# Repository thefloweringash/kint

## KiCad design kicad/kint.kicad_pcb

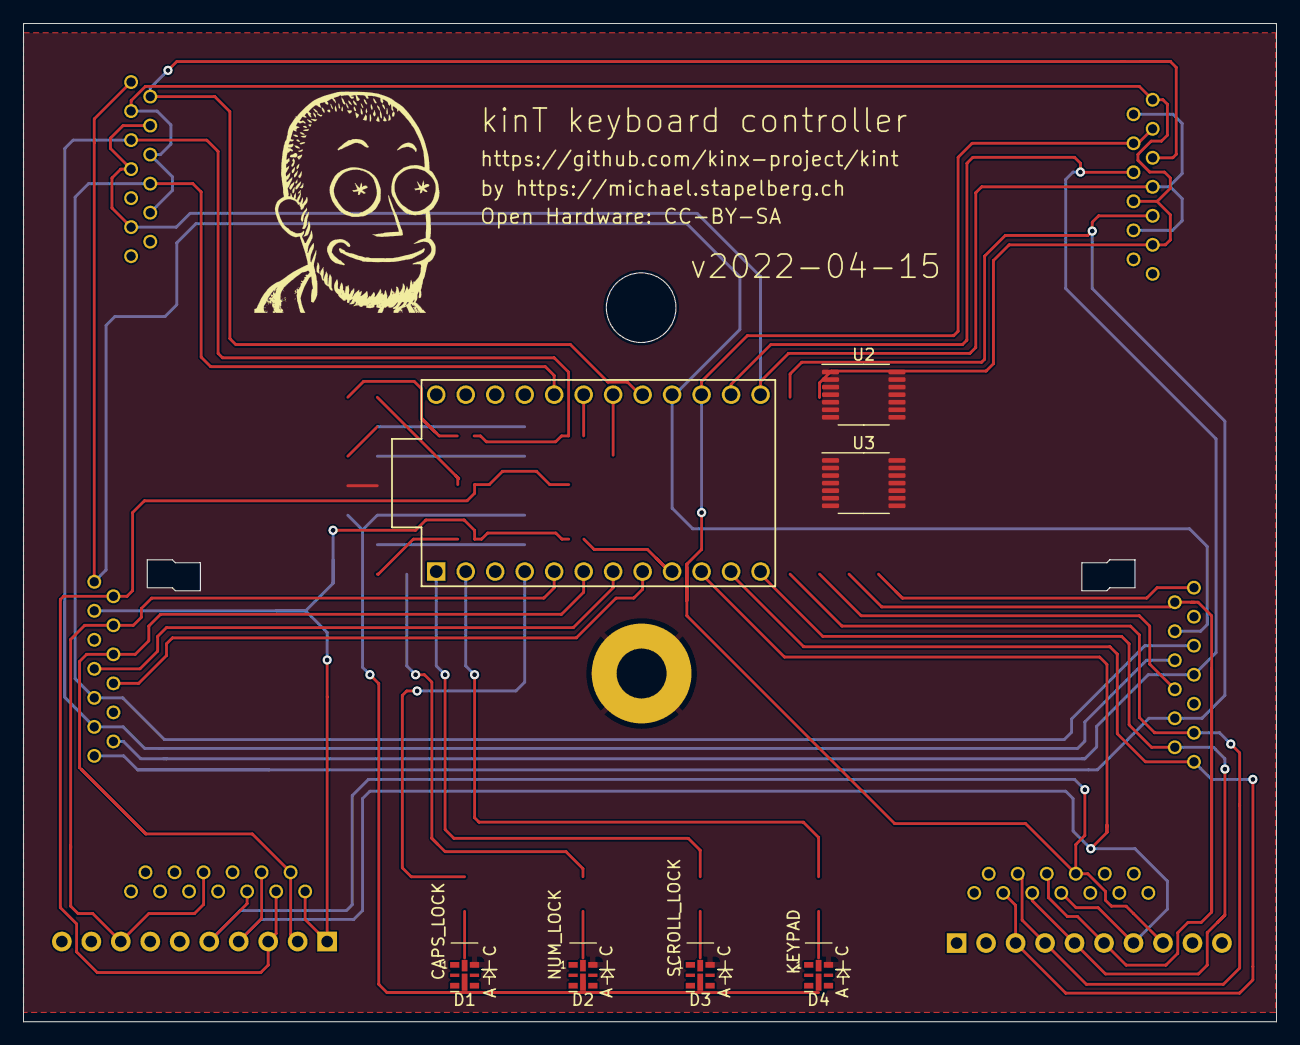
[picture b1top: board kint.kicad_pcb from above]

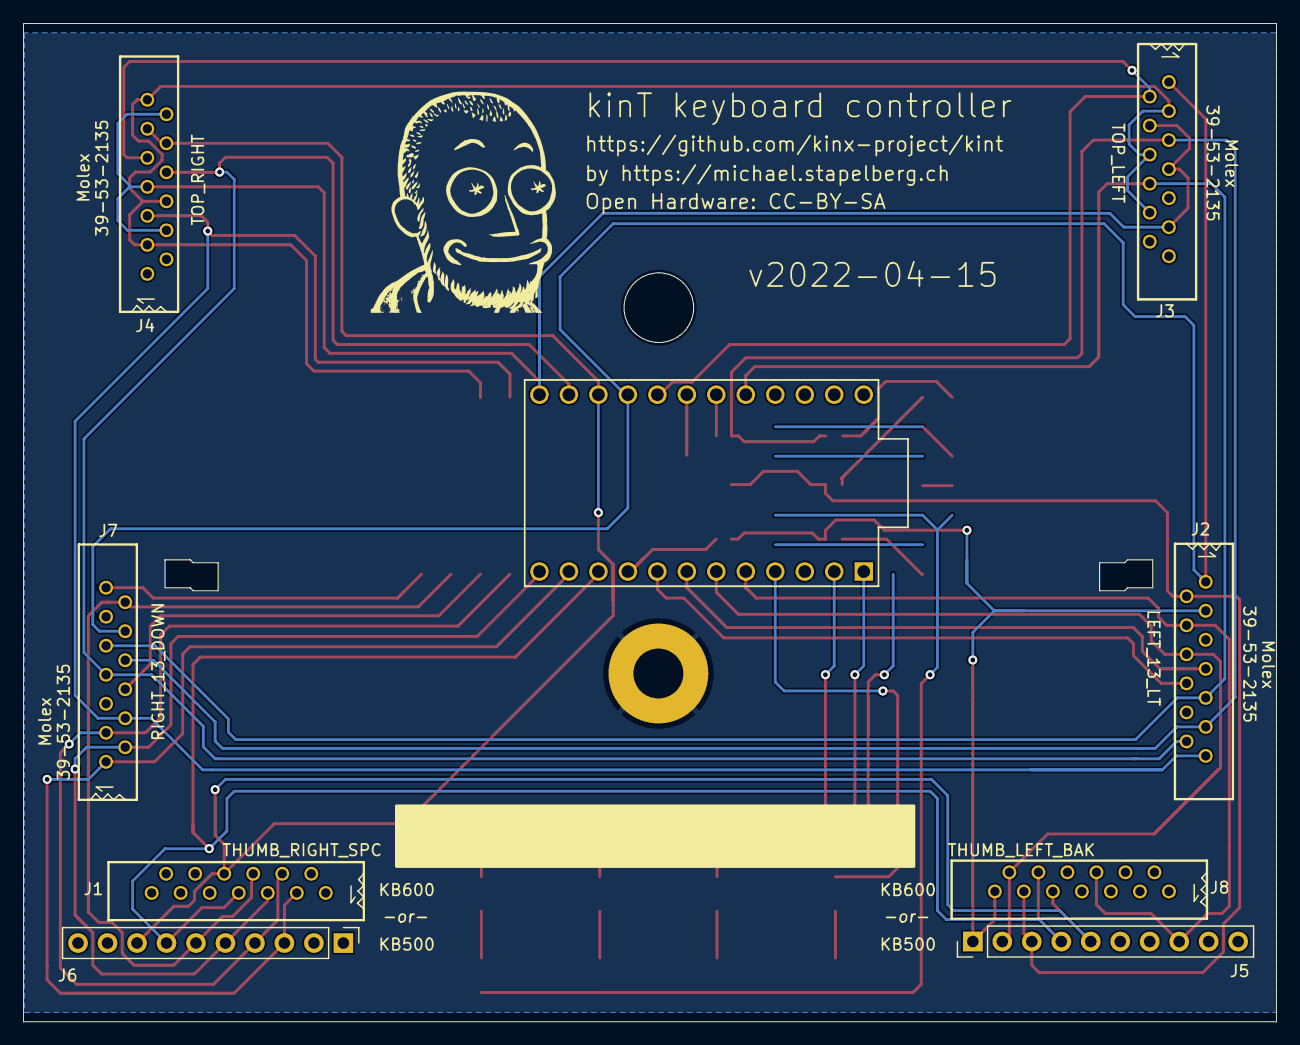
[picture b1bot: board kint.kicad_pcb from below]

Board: 2 copper layers, 107.9 x 86.0 mm, 17 parts (8 on the bottom side), 35 nets.

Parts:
D1, D2, D3, D4: APA102-2020; LED-APA102-2020
H1: mounting pad; MountingHole_4.3mm_M4_Pad
H2: mounting pad; MountingHole_6mm
J1: THUMB_RIGHT_SPC_KB600; 39-53-2135
J2: LEFT_13_LT; 39-53-2135
J3: TOP_LEFT; 39-53-2135
J4: TOP_RIGHT; 39-53-2135
J5: THUMB_LEFT_BAK; PinHeader_1x10_P2.54mm_Vertical
J6: THUMB_RIGHT_SPC; PinHeader_1x10_P2.54mm_Vertical
J7: RIGHT_13_DOWN; 39-53-2135
J8: THUMB_LEFT_BAK_KB600; 39-53-2135
U1: ProMicro
U2, U3: 74HC164; TSSOP-14_4.4x5mm_P0.65mm

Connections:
/5V: D1.1 (VDD), D2.1 (VDD), D3.1 (VDD), D4.1 (VDD)
/COL_0: J2.1, J3.1, J7.10, U1.20 (F4)
/COL_1: J2.9, J3.8, J7.9, U1.19 (F5)
/COL_2: J2.11, J3.5, J7.8, U1.18 (F6)
/COL_3: J2.12, J4.8, J7.7, U1.17 (F7)
/COL_4: J2.13, J4.5, J7.4, U1.16 (B1)
/COL_5: J1.8, J4.10, J4.11, J5.5, J6.8, J8.9, U1.15 (B3)
/COL_6: J1.7, J5.4, J6.7, J8.10, U1.14 (B2)
/LED_CLOCK: D1.5 (CKI), U1.6 (SCL)
/LED_DATA: D1.4 (SDI), U1.5 (SDA)
/ROW_0: J7.13, U2.3 (Q0)
/ROW_1: J2.7, U2.4 (Q1)
/ROW_2: J2.6, J5.2, J8.12, U2.5 (Q2)
/ROW_3: J2.4, J5.8, J8.6, U2.6 (Q3)
/ROW_4: J2.3, J5.1, J8.13, U2.10 (Q4)
/ROW_5: J2.2, J5.3, J8.11, U2.11 (Q5)
/ROW_6: J1.3, J6.3, J7.1, U2.12 (Q6)
/ROW_7: J1.4, J6.4, J7.3, U2.13 (Q7), U3.1 (DSA)
/ROW_8: J1.5, J6.5, J7.2, U3.3 (Q0)
/ROW_9: J1.6, J6.6, J7.12, U3.4 (Q1)
/ROW_CLOCK: U1.10 (E6), U2.8 (CP), U3.8 (CP)
/ROW_DATA: U1.9 (D7), U2.1 (DSA)
/ROW_EQL: J2.8, U3.12 (Q6)
/ROW_ESC: J3.2, J4.9, U3.11 (Q5)
/ROW_F1: J3.3, J3.6, J3.10, J4.3, J4.6, J4.13, U3.5 (Q2)
/ROW_F2: J3.4, J3.7, J3.11, J4.4, J4.7, J4.12, U3.6 (Q3)
/ROW_MIN: J7.6, U3.10 (Q4)
/VCC: U2.14 (VCC), U3.14 (VCC)
GND: D1.6 (GND), D2.6 (GND), D3.6 (GND), D4.6 (GND), H1.1, U1.3 (GND), U1.4 (GND), U1.23 (GND), U2.7 (GND), U3.7 (GND)
unnamed: D1.2 (CKO), D2.5 (CKI)
unnamed: D1.3 (SDO), D2.4 (SDI)
unnamed: D2.2 (CKO), D3.5 (CKI)
unnamed: D2.3 (SDO), D3.4 (SDI)
unnamed: D3.2 (CKO), D4.5 (CKI)
unnamed: D3.3 (SDO), D4.4 (SDI)

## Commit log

2022-09-23 Add ProMicro resources
2022-09-23 [WIP] playing around with promicro compatibility

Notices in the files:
kicad/kint.kicad_pcb:
Open Hardware: CC-BY-SA
